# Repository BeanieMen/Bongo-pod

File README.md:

## BONGO PODDD :3

i love yall at build guild delhi :DD
oki so i build bongo pod which is music player
i hope yall likey :}

made with love by beanie man aka ajju aka aarjav jain!!! :>

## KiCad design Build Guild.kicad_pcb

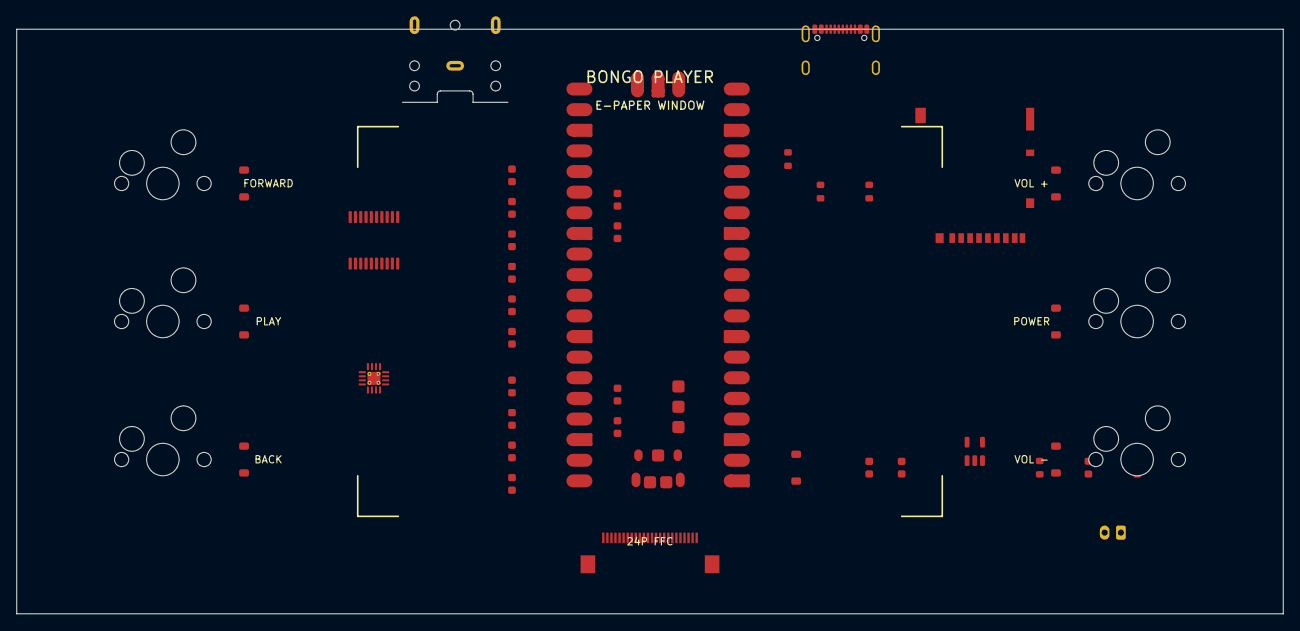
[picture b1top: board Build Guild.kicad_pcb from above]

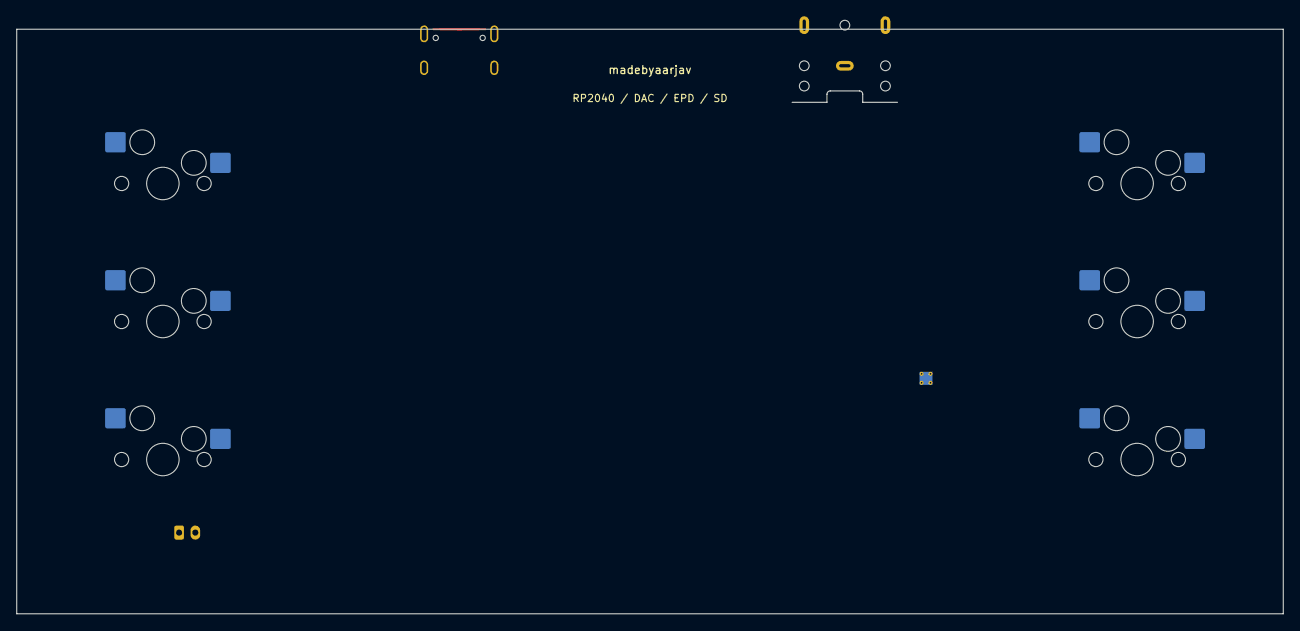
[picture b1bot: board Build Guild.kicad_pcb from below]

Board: 2 copper layers, 156.0 x 72.0 mm, 44 parts (35 on the bottom side), 39 nets.

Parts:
A1: RaspberryPi_Pico_SMD
C1, C2, C3, C4, C5, C6, C7, C8, C9, C10, C11, C12, C13, C14, C15, C16: C_0603_1608Metric
D1, D3, D4, D5, D6, D7, D8: D_SOD-123
D2: LED_0603_1608Metric
J1: USB_C_Receptacle_GCT_USB4105-xx-A_16P_TopMnt_Hori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; USB_C_Receptacle_GCT_USB4105-xx-A_16P_TopMnt_Horizontal
J2: JST_PH_B2B-PH-K_1x02_P2.00mm_Vertical
J3: Jack_3.5mm_CUI_SJ1-3523N_Horizontal
J4: microSD_HC_Hirose_DM3AT-SF-PEJM5
J5: Hirose_FH12-24S-0.5SH_1x24-1MP_P0.50mm_Horizontal
R1, R2, R3, R4, R5: R_0603_1608Metric
SW1, SW2, SW3, SW4, SW5, SW6: SW_Hotswap_Kailh_MX_1.00u
U1: SOT-23-5
U2: TSSOP-20_4.4x6.5mm_P0.65mm
U3: WQFN-16-1EP_3x3mm_P0.5mm_EP1.6x1.6mm_ThermalVias

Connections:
+3.3V: A1.35, A1.36, C7.1, C8.1, C9.1, C10.1, C15.1, C16.1, J4.4, J5.2, J5.9, R4.1, U2.1, U2.8, U2.17, U2.20, U3.12, U3.13, U3.14
AMP_CPN: C12.2, U3.9
AMP_CPP: C12.1, U3.11
AMP_NEG: C11.1, U3.8
CHG_PROG: R3.1, U1.5
CHG_STAT: D2.2, R4.2, U1.1
COL0: A1.21, D5.1, D5.2
COL1: A1.22, D6.1, D6.2, D8.1, D8.2
DAC_L: C13.1, U2.6
DAC_R: C14.1, U2.7
EPD_BUSY: A1.11, J5.6
EPD_CS: A1.7, J5.3
EPD_DC: A1.9, J5.4
EPD_RST: A1.10, J5.5
GND: A1.3, A1.8, A1.13, A1.18, A1.23, A1.28, A1.33, A1.38, A1.D2, A1.TP1, C1.2, C2.2, C3.2, C5.2, C6.2, C7.2, C9.2, C10.2, C11.2, C13.2, C14.2, C15.2, C16.2, D2.1, J1.A1, J1.A12, J1.B1, J1.B12, J1.S1, J2.2, J4.6, J4.11, J5.1, J5.10, R1.2, R3.2, R5.1, U1.2, U2.3, U2.9, U2.10, U2.11, U2.12, U2.16, U2.19, U3.1, U3.4, U3.6, U3.7, U3.10, U3.15, U3.17
I2S_BCK: A1.14, U2.13
I2S_DOUT: A1.16, U2.14
I2S_LRCK: A1.15, U2.15
PCM_CAPM: C4.2, U2.4
PCM_CAPP: C4.1, U2.2
PCM_LDO: C6.1, U2.18
PCM_VNEG: C5.1, U2.5
ROW0: A1.17, SW1.1, SW4.1
ROW1: A1.19, SW2.1, SW5.1
ROW2: A1.20, SW3.1, SW6.1
SD_CS: A1.12, J4.2, R5.2
SD_DET: A1.25, J4.10
SPI_MISO: A1.6, J4.7
SPI_MOSI: A1.5, J4.3, J5.8
SPI_SCK: A1.4, C8.2, J4.5, J5.7
SW1_NODE: D3.1, D3.2, SW1.2
SW2_NODE: D4.1, D4.2, SW2.2
SW5_NODE: D7.1, D7.2, SW5.2
USB_CC1: J1.A5, R1.1, R2.2
USB_CC2: J1.B5, R2.1
USB_DM: A1.TP2, J1.A7, J1.B7
USB_DP: A1.TP3, J1.A6, J1.B6
VBUS: A1.40, C1.1, D1.1, D1.2, J1.A4, J1.A9, J1.B4, J1.B9, U1.4
VSYS: A1.39, C2.1, J2.1, U1.3
